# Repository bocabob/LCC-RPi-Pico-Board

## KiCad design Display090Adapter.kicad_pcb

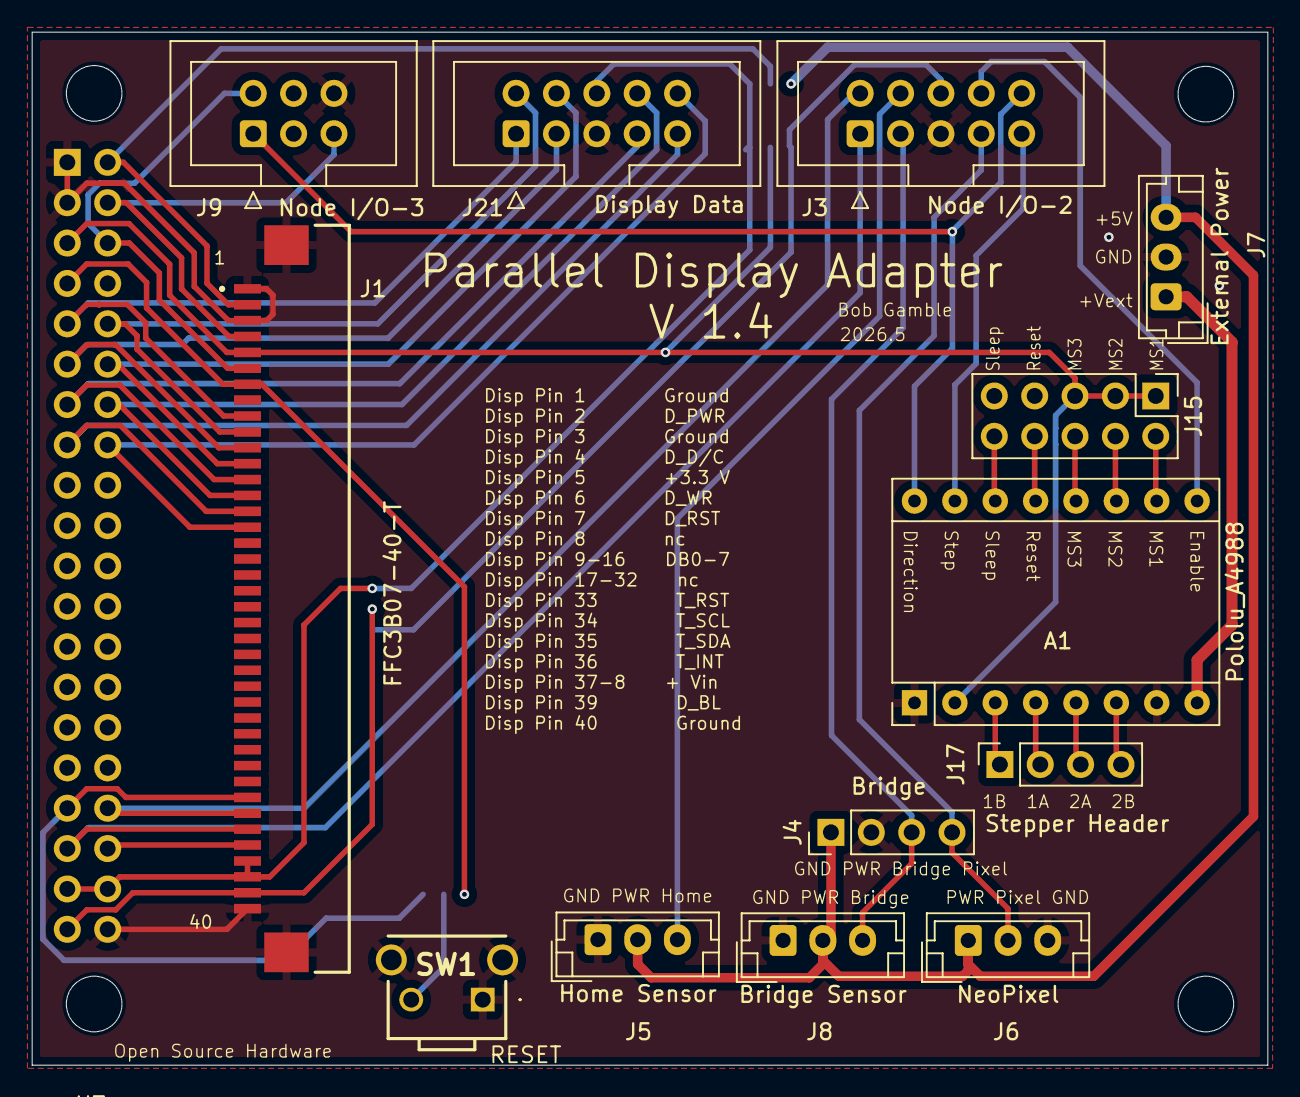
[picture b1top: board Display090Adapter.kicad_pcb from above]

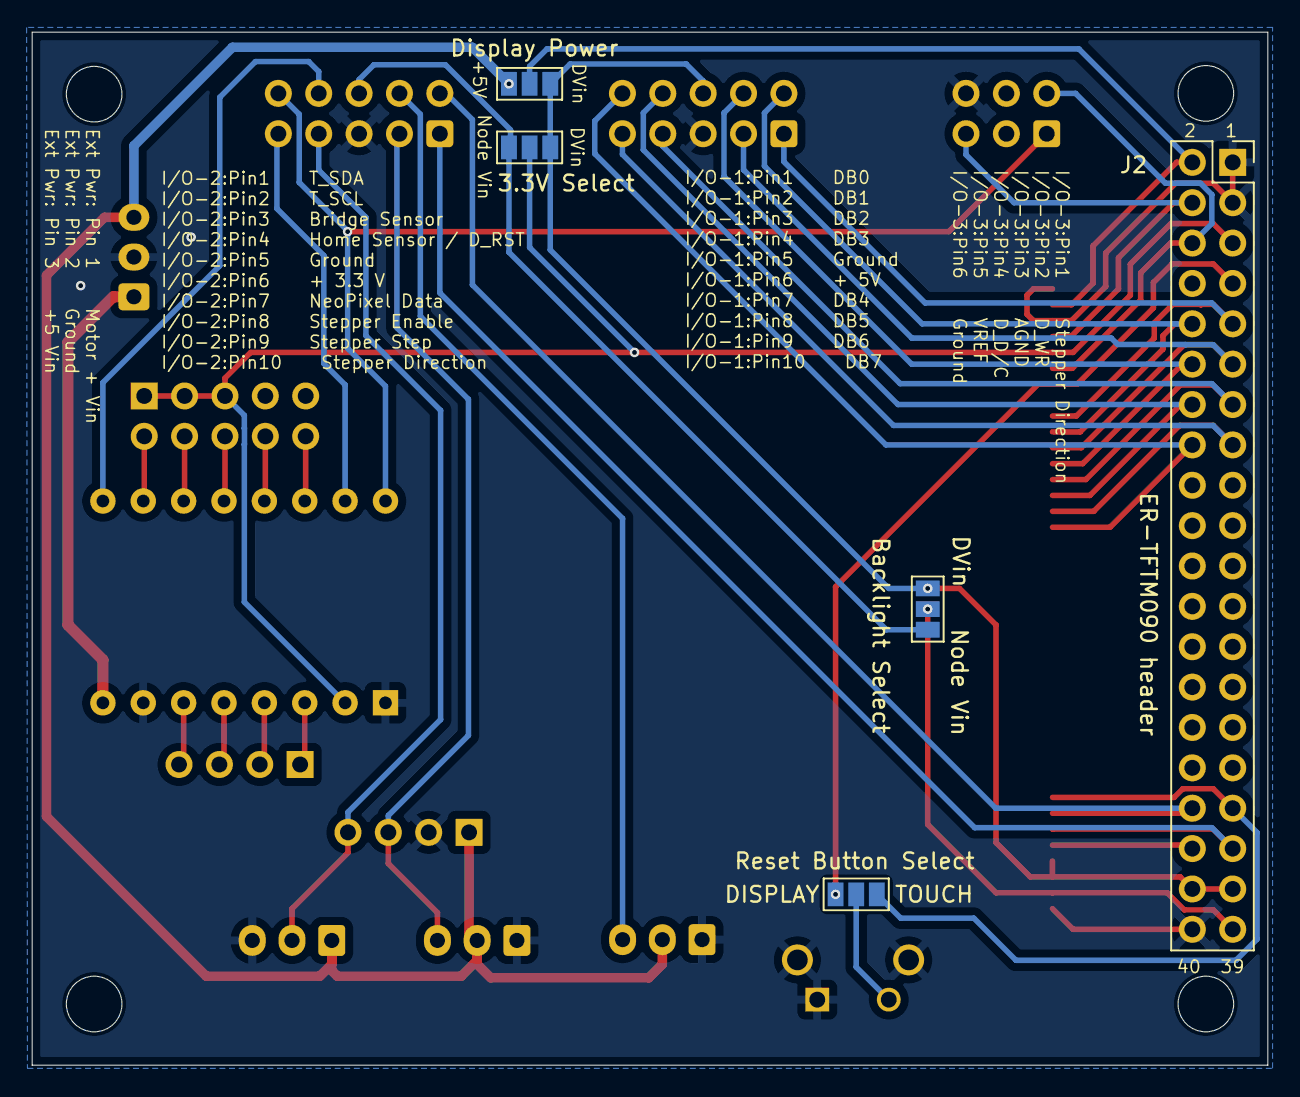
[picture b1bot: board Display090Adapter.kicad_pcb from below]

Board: 2 copper layers, 77.8 x 65.0 mm, 22 parts (5 on the bottom side), 39 nets.

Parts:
A1: Pololu_A4988; Pololu_Breakout-16_15.2x20.3mm
H1, H2, H3, H4: MountingHole; MountingHole_3.5mm
J1: FFC3B07-40-T; GCT_FFC3B07-40-T
J2: ER-TFTM090 header; PinSocket_2x20_P2.54mm_Vertical
J3: Node I/O-2; IDC-Header_2x05_P2.54mm_Vertical
J4: Bridge; PinHeader_1x04_P2.54mm_Vertical
J5: Home Sensor; JST_EH_B3B-EH-A_1x03_P2.50mm_Vertical
J6: NeoPixel; JST_EH_B3B-EH-A_1x03_P2.50mm_Vertical
J7: External Power; JST_EH_B3B-EH-A_1x03_P2.50mm_Vertical
J8: Bridge Sensor; JST_EH_B3B-EH-A_1x03_P2.50mm_Vertical
J9: Node I/O-3; IDC-Header_2x03_P2.54mm_Vertical
J15: Conn_02x05_Odd_Even; PinHeader_2x05_P2.54mm_Vertical
J17: Stepper Header; PinSocket_1x04_P2.54mm_Vertical
J21: Display Data; IDC-Header_2x05_P2.54mm_Vertical
JP1: Backlight Select; SolderJumper-3_P1.3mm_Open_Pad1.0x1.5mm_NumberLabels
JP2: Display Power; SolderJumper-3_P1.3mm_Open_Pad1.0x1.5mm_NumberLabels
JP3: Reset Button Select; SolderJumper-3_P1.3mm_Open_Pad1.0x1.5mm_NumberLabels
JP4: 3.3V Select; SolderJumper-3_P1.3mm_Open_Pad1.0x1.5mm_NumberLabels
SW1: Display Reset; TS1167443BK160RAD

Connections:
+3V3: A1.2 (VDD), J1.5, J2.5, J15.1, J15.3, J15.5, JP4.2 (C)
+5V: J4.1, J5.2, J6.1, J7.3, J8.2, JP2.3 (B)
+VIN: J1.37, J1.38, J2.37, J2.38, J21.6, JP1.1 (A), JP2.1 (A), JP4.1 (A)
BRIDGE: J3.3, J4.3, J8.3
DB0: J1.9, J2.9, J21.1
DB1: J1.10, J2.10, J21.2
DB2: J1.11, J2.11, J21.3
DB3: J1.12, J2.12, J21.4
DB4: J1.13, J2.13, J21.7
DB5: J1.14, J2.14, J21.8
DB6: J1.15, J2.15, J21.9
DB7: J1.16, J2.16, J21.10
DIRECTION: A1.16 (DIR), J3.10, J9.1
D_BL: J1.39, J2.39, JP1.2 (C)
D_D/C: J1.4, J2.4, J9.5
D_PWR: J1.2, J2.2, JP2.2 (C)
D_RST: J1.7, J2.7, JP3.3 (B)
D_WR: J1.6, J2.6, J9.2
ENABLE: A1.9 (~ENABLE), J3.8
GND: A1.1 (GND), A1.7 (GND), J1.1, J1.3, J1.40, J1.S1 (SHIELD), J1.S2 (SHIELD), J2.1, J2.3, J2.40, J3.5, J4.2, J5.1, J6.3, J7.2, J8.1, J9.6, J21.5, SW1.1 (COM), SW1.3 (GND_1), SW1.4 (GND_2)
GP19: J3.4, J5.3
GP20: J3.7, J4.4, J6.2
GP22: A1.15 (STEP), J3.9
unnamed: A1.4 (1A), J17.2
unnamed: A1.3 (1B), J17.1
unnamed: A1.5 (2A), J17.3
unnamed: A1.6 (2B), J17.4
unnamed: A1.10 (MS1), J15.2
unnamed: A1.11 (MS2), J15.4
unnamed: A1.12 (MS3), J15.6
unnamed: A1.13 (~RESET), J15.8
unnamed: A1.14 (~SLEEP), J15.10
unnamed: JP3.2 (C), SW1.2 (NO)
SCL0: J1.34, J2.34, J3.2
SDA0: J1.35, J2.35, J3.1
SVin: J3.6, JP1.3 (B), JP4.3 (B)
T_INT: J1.36, J2.36
T_RST: J1.33, J2.33, JP3.1 (A)
VEXT: A1.8 (VMOT), J7.1

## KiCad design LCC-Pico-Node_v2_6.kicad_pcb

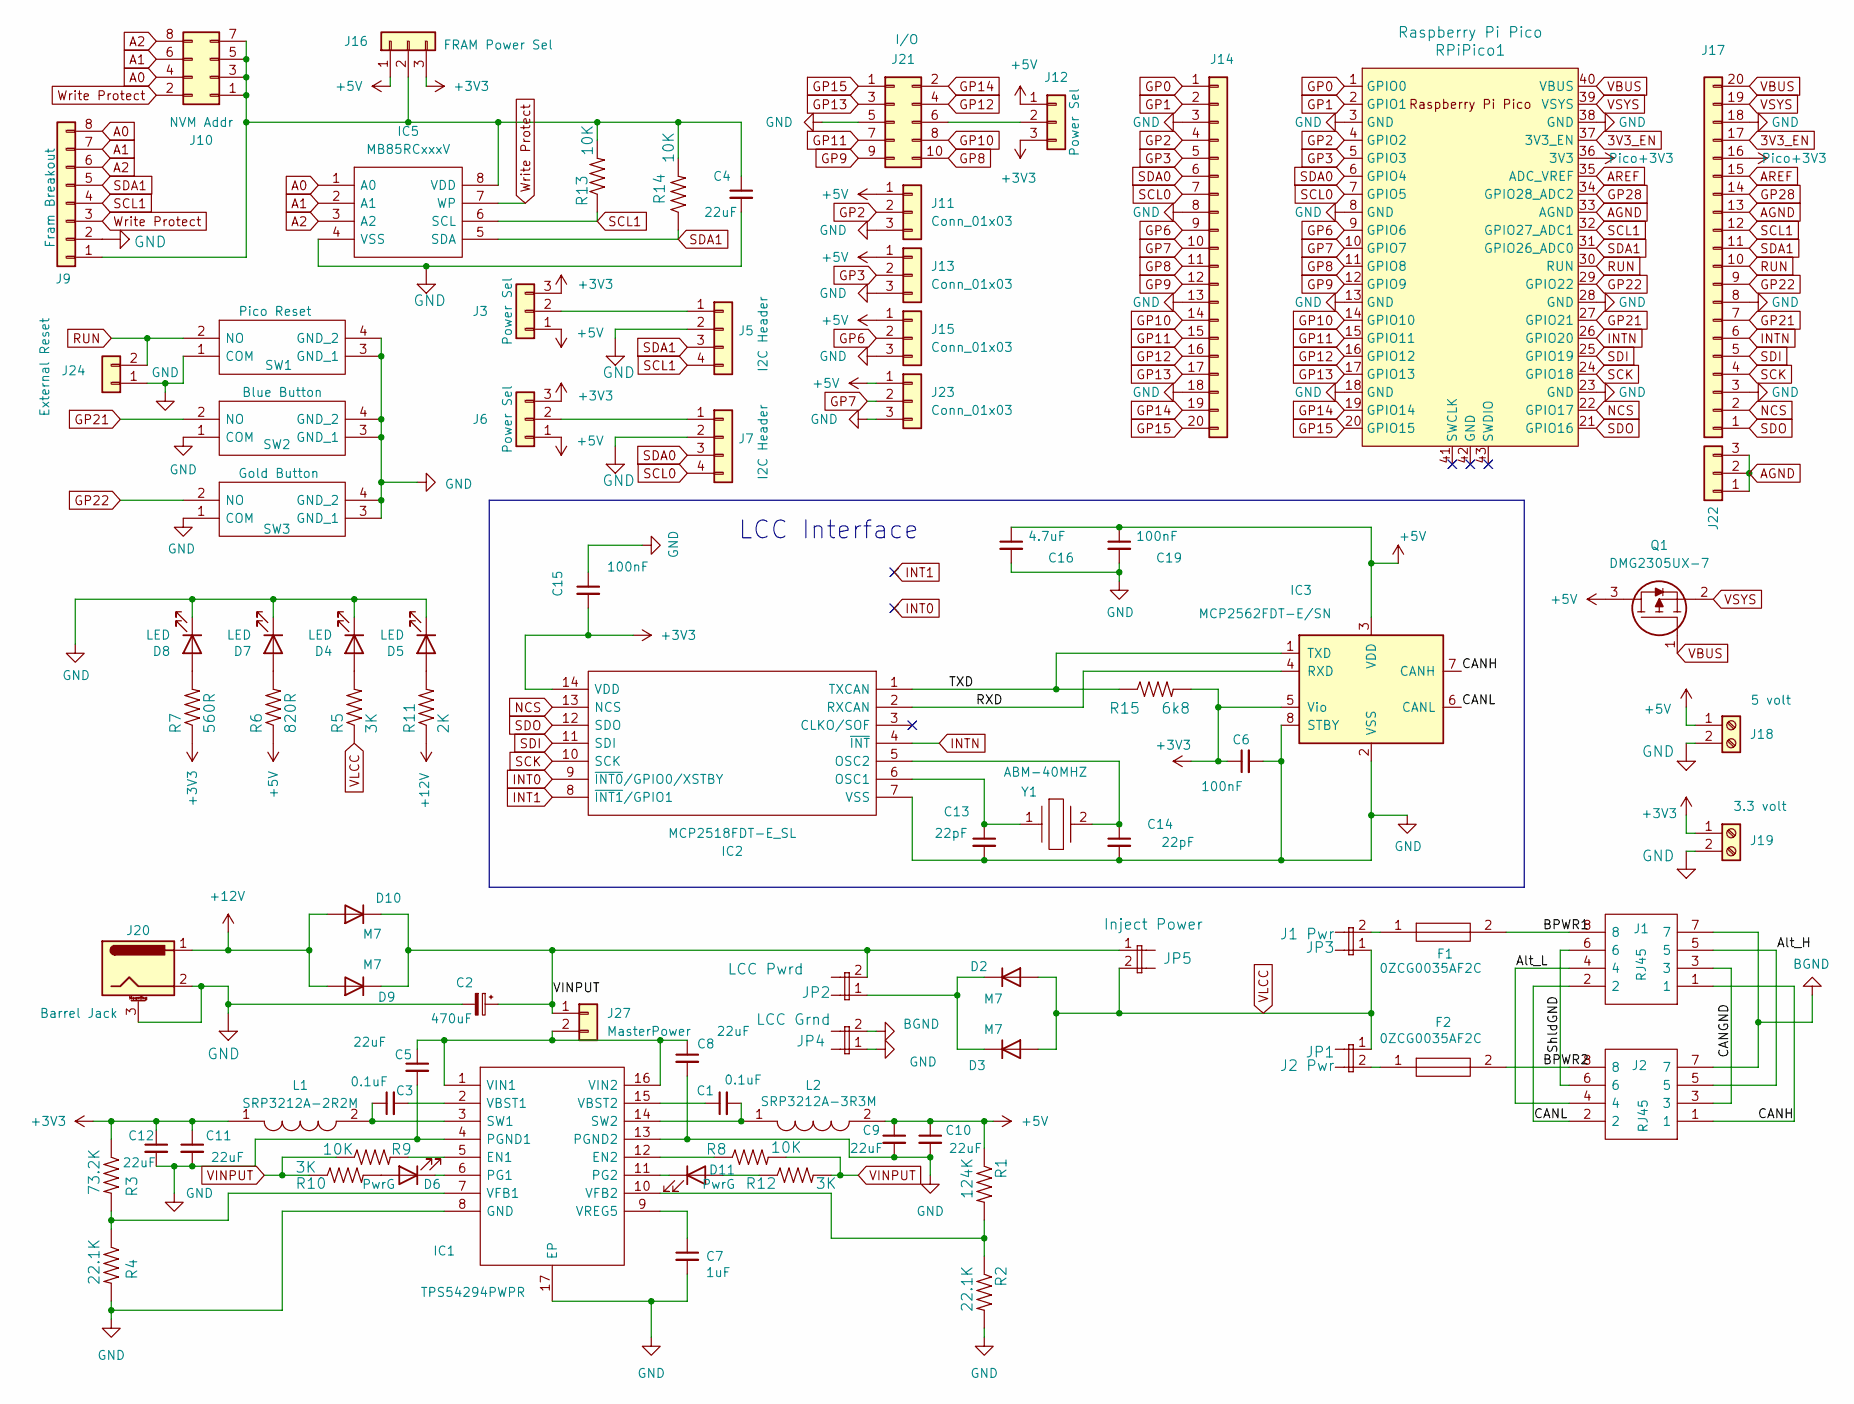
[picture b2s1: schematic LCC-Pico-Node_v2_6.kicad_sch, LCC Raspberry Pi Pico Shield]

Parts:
C1, C3: 0.1uF; C_1206_3216Metric_Pad1.33x1.80mm_HandSolder
C2: 470uF; CP_Radial_D8.0mm_P3.50mm
C4, C5, C8, C9, C10, C11, C12: 22uF; C_1206_3216Metric_Pad1.33x1.80mm_HandSolder
C6, C15, C19: 100nF; C_1206_3216Metric_Pad1.33x1.80mm_HandSolder
C7: 1uF; C_1206_3216Metric_Pad1.33x1.80mm_HandSolder
C13, C14: 22pF; C_1206_3216Metric_Pad1.33x1.80mm_HandSolder
C16: 4.7uF; C_1206_3216Metric_Pad1.33x1.80mm_HandSolder
D2, D3, D9, D10: M7; DIOM5327X240N
D4, D5, D7, D8: LED; LED_1206_3216Metric_Pad1.42x1.75mm_HandSolder
D6, D11: PwrG; LED_1206_3216Metric_Pad1.42x1.75mm_HandSolder
F1, F2: 0ZCG0035AF2C; FUSC4632X70N; Mouser Part Number 530-0ZCG0035AF2C
IC1: TPS54294PWPR; SOP65P640X120-17N; Mouser Part Number 595-TPS54294PWPR
IC2: MCP2518FDT-E_SL; SOIC-14_3.9x8.7mm_P1.27mm; Mouser Part Number 579-MCP2518FDT-E/SL
IC3: MCP2562FDT-E/SN; SOIC-8_3.9x4.9mm_P1.27mm; Mouser Part Number 771-TJA1042T/3/1J
IC5: MB85RCxxxV; SOIC127P600X175-8N; Mouser Part Number 249-MB85RC256VPNJNE1
J1, J2: RJ45; MTJ880X1; Mouser Part Number 737-MTJ-880X1
J3, J6, J12: Power Sel; PinHeader_1x03_P2.54mm_Vertical
J5, J7: I2C Header; PinSocket_1x04_P2.54mm_Vertical
J9: Fram Breakout; PinHeader_1x08_P2.54mm_Vertical
J10: NVM Addr; PinHeader_2x04_P2.54mm_Vertical
J11, J13, J15, J23: Conn_01x03; JST_XH_B3B-XH-A_1x03_P2.50mm_Vertical
J14, J17: Conn_01x20; PinHeader_1x20_P2.54mm_Vertical
J16: FRAM Power Sel; SolderJumper-3_P1.3mm_Open_RoundedPad1.0x1.5mm
J18: 5 volt; TerminalBlock_TE_282834-2_1x02_P2.54mm_Horizontal
J19: 3.3 volt; TerminalBlock_TE_282834-2_1x02_P2.54mm_Horizontal
J20: Barrel Jack; BarrelJack_Horizontal
J21: I/O; IDC-Header_2x05_P2.54mm_Vertical
J22: AGND; PinHeader_1x03_P2.54mm_Vertical
J24: External Reset; PinHeader_1x02_P2.54mm_Vertical
J27: MasterPower; PinHeader_1x02_P2.54mm_Vertical
JP1: J2 Pwr; PinHeader_1x02_P2.54mm_Vertical
JP2: LCC Pwrd; PinHeader_1x02_P2.54mm_Vertical
JP3: J1 Pwr; PinHeader_1x02_P2.54mm_Vertical
JP4: LCC Grnd; PinHeader_1x02_P2.54mm_Vertical
JP5: Inject Power; PinHeader_1x02_P2.54mm_Vertical
L1: SRP3212A-2R2M; INDC3225X120N; Mouser Part Number 652-SRP3212A-3R3M
L2: SRP3212A-3R3M; INDC3225X120N; Mouser Part Number 652-SRP3212A-3R3M
Q1: DMG2305UX-7; SOT96P240X115-3N; Mouser Part Number 621-DMG2305UX-7
R1: 124K; R_1206_3216Metric_Pad1.30x1.75mm_HandSolder
R2, R4: 22.1K; R_1206_3216Metric_Pad1.30x1.75mm_HandSolder
R3: 73.2K; R_1206_3216Metric_Pad1.30x1.75mm_HandSolder
R5, R10, R12: 3K; R_1206_3216Metric_Pad1.30x1.75mm_HandSolder
R6: 820R; R_1206_3216Metric_Pad1.30x1.75mm_HandSolder
R7: 560R; R_1206_3216Metric_Pad1.30x1.75mm_HandSolder
R8, R9, R13, R14: 10K; R_1206_3216Metric_Pad1.30x1.75mm_HandSolder
R11: 2K; R_1206_3216Metric_Pad1.30x1.75mm_HandSolder
R15: 6k8; R_1206_3216Metric_Pad1.30x1.75mm_HandSolder
RPiPico1: Raspberry Pi Pico; RPi_Pico_SMD_TH; PARTREV 12/May/2017
SW1: Pico Reset; TS1167443BK160RAD; Mouser Part Number 179-TS1167443160RAD
SW2: Blue Button; TS1167443BK160RAD; Mouser Part Number 179-TS1167443160RAD
SW3: Gold Button; TS1167443BK160RAD; Mouser Part Number 179-TS1167443160RAD
Y1: ABM-40MHZ; ABM3; Mouser Part Number 815-ABL-40-B2F

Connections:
3V3_EN: J17.17, RPiPico1.37 (3V3_EN)
+3V3: C6.1, C11.1, C12.1, C15.2, IC2.14 (VDD), IC3.5 (Vio), J3.3, J6.3, J12.3, J16.3, J19.1, L1.1, R3.1, R7.1, R15.2
+5V: C9.1, C10.1, C16.1, C19.1, IC3.3 (VDD), J3.1, J6.1, J11.1, J12.1, J13.1, J15.1, J16.1, J18.1, J23.1, L2.2, Q1.3, R1.1, R6.1
+12V: D9.2 (A), D10.2 (A), J20.1, R11.1
/Alt_H: J1.5, J2.5
/Alt_L: J1.4, J2.4
/BPWR1: F1.2, J1.8
/BPWR2: F2.2, J2.8
/CANGND: J1.3, J2.3
/CANH: IC3.7 (CANH), J1.1, J2.1
/CANL: IC3.6 (CANL), J1.2, J2.2
/RXD: IC2.2 (RXCAN), IC3.4 (RXD)
/ShldGND: J1.6, J2.6
/TXD: IC2.1 (TXCAN), IC3.1 (TXD), R15.1
A0: IC5.1 (A0), J9.8, J10.4
A1: IC5.2 (A1), J9.7, J10.6
A2: IC5.3 (A2), J9.6, J10.8
AGND: J17.13, J22.1, J22.2, J22.3, RPiPico1.33 (AGND)
AREF: J17.15, RPiPico1.35 (ADC_VREF)
BGND: J1.7, J2.7, JP4.2
GND: C2.2, C4.2, C5.2, C6.2, C7.2, C8.2, C9.2, C10.2, C11.2, C12.2, C13.2, C14.2, C15.1, C16.2, C19.2, D4.1 (K), D5.1 (K), D7.1 (K), D8.1 (K), IC1.4 (PGND1), IC1.8 (GND), IC1.13 (PGND2), IC1.17 (EP), IC2.7 (VSS), IC3.2 (VSS), IC3.8 (STBY), IC5.4 (VSS), J5.2, J7.2, J9.2, J11.3, J13.3, J14.3, J14.8, J14.13, J14.18, J15.3, J17.3, J17.8, J17.18, J18.2, J19.2, J20.2, J20.3, J21.5, J23.3, J24.1, JP4.1, R2.2, R4.2, RPiPico1.3 (GND), RPiPico1.8 (GND), RPiPico1.13 (GND), RPiPico1.18 (GND), RPiPico1.23 (GND), RPiPico1.28 (GND), RPiPico1.38 (GND), SW1.1 (COM), SW1.3 (GND_1), SW1.4 (GND_2), SW2.1 (COM), SW2.3 (GND_1), SW2.4 (GND_2), SW3.1 (COM), SW3.3 (GND_1), SW3.4 (GND_2)
GP0: J14.1, RPiPico1.1 (GPIO0)
GP1: J14.2, RPiPico1.2 (GPIO1)
GP2: J11.2, J14.4, RPiPico1.4 (GPIO2)
GP3: J13.2, J14.5, RPiPico1.5 (GPIO3)
GP6: J14.9, J15.2, RPiPico1.9 (GPIO6)
GP7: J14.10, J23.2, RPiPico1.10 (GPIO7)
GP8: J14.11, J21.10, RPiPico1.11 (GPIO8)
GP9: J14.12, J21.9, RPiPico1.12 (GPIO9)
GP10: J14.14, J21.8, RPiPico1.14 (GPIO10)
GP11: J14.15, J21.7, RPiPico1.15 (GPIO11)
GP12: J14.16, J21.4, RPiPico1.16 (GPIO12)
GP13: J14.17, J21.3, RPiPico1.17 (GPIO13)
GP14: J14.19, J21.2, RPiPico1.19 (GPIO14)
GP15: J14.20, J21.1, RPiPico1.20 (GPIO15)
GP21: J17.7, RPiPico1.27 (GPIO21), SW2.2 (NO)
GP22: J17.9, RPiPico1.29 (GPIO22), SW3.2 (NO)
GP28: J17.14, RPiPico1.34 (GPIO28_ADC2)
INT0: IC2.9 (~INT0/GPIO0/XSTBY)
INT1: IC2.8 (~INT1/GPIO1)
INTN: IC2.4 (~INT), J17.6, RPiPico1.26 (GPIO20)
NCS: IC2.13 (NCS), J17.2, RPiPico1.22 (GPIO17)
unnamed: D2.1 (K), D3.1 (K), JP2.1
unnamed: D4.2 (A), R5.2
unnamed: D5.2 (A), R11.2
unnamed: D6.2 (A), R10.2
unnamed: D6.1 (K), IC1.6 (PG1)
unnamed: D7.2 (A), R6.2
unnamed: D8.2 (A), R7.2
unnamed: D11.2 (A), R12.1
unnamed: D11.1 (K), IC1.11 (PG2)
unnamed: F1.1, JP3.2
unnamed: F2.1, JP1.2
unnamed: IC1.5 (EN1), R9.2
unnamed: IC1.12 (EN2), R8.1
unnamed: C3.1, IC1.3 (SW1), L1.2
unnamed: C1.2, IC1.14 (SW2), L2.1
unnamed: C3.2, IC1.2 (VBST1)
unnamed: C1.1, IC1.15 (VBST2)
unnamed: IC1.7 (VFB1), R3.2, R4.1
unnamed: IC1.10 (VFB2), R1.2, R2.1
unnamed: C5.1, C8.1, IC1.1 (VIN1), IC1.16 (VIN2), J27.2
unnamed: C7.1, IC1.9 (VREG5)
unnamed: C13.1, IC2.6 (OSC1), Y1.1
unnamed: C14.1, IC2.5 (OSC2), Y1.2
unnamed: C4.1, IC5.8 (VDD), J9.1, J10.1, J10.3, J10.5, J10.7, J16.2, R13.2, R14.2
unnamed: J3.2, J5.1
unnamed: J6.2, J7.1
unnamed: J12.2, J21.6
Pico+3V3: J17.16, RPiPico1.36 (3V3)
RUN: J17.10, J24.2, RPiPico1.30 (RUN), SW1.2 (NO)
SCK: IC2.10 (SCK), J17.4, RPiPico1.24 (GPIO18)
SCL0: J7.4, J14.7, RPiPico1.7 (GPIO5)
SCL1: IC5.6 (SCL), J5.4, J9.4, J17.12, R13.1, RPiPico1.32 (GPIO27_ADC1)
SDA0: J7.3, J14.6, RPiPico1.6 (GPIO4)
SDA1: IC5.5 (SDA), J5.3, J9.5, J17.11, R14.1, RPiPico1.31 (GPIO26_ADC0)
SDI: IC2.11 (SDI), J17.5, RPiPico1.25 (GPIO19)
SDO: IC2.12 (SDO), J17.1, RPiPico1.21 (GPIO16)
VBUS: J17.20, Q1.1, RPiPico1.40 (VBUS)
VINPUT: C2.1, D9.1 (K), D10.1 (K), J27.1, JP2.2, JP5.1, R8.2, R9.1, R10.1, R12.2
VLCC: D2.2 (A), D3.2 (A), JP1.1, JP3.1, JP5.2, R5.1
VSYS: J17.19, Q1.2, RPiPico1.39 (VSYS)
Write Protect: IC5.7 (WP), J9.3, J10.2

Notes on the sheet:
LCC Interface

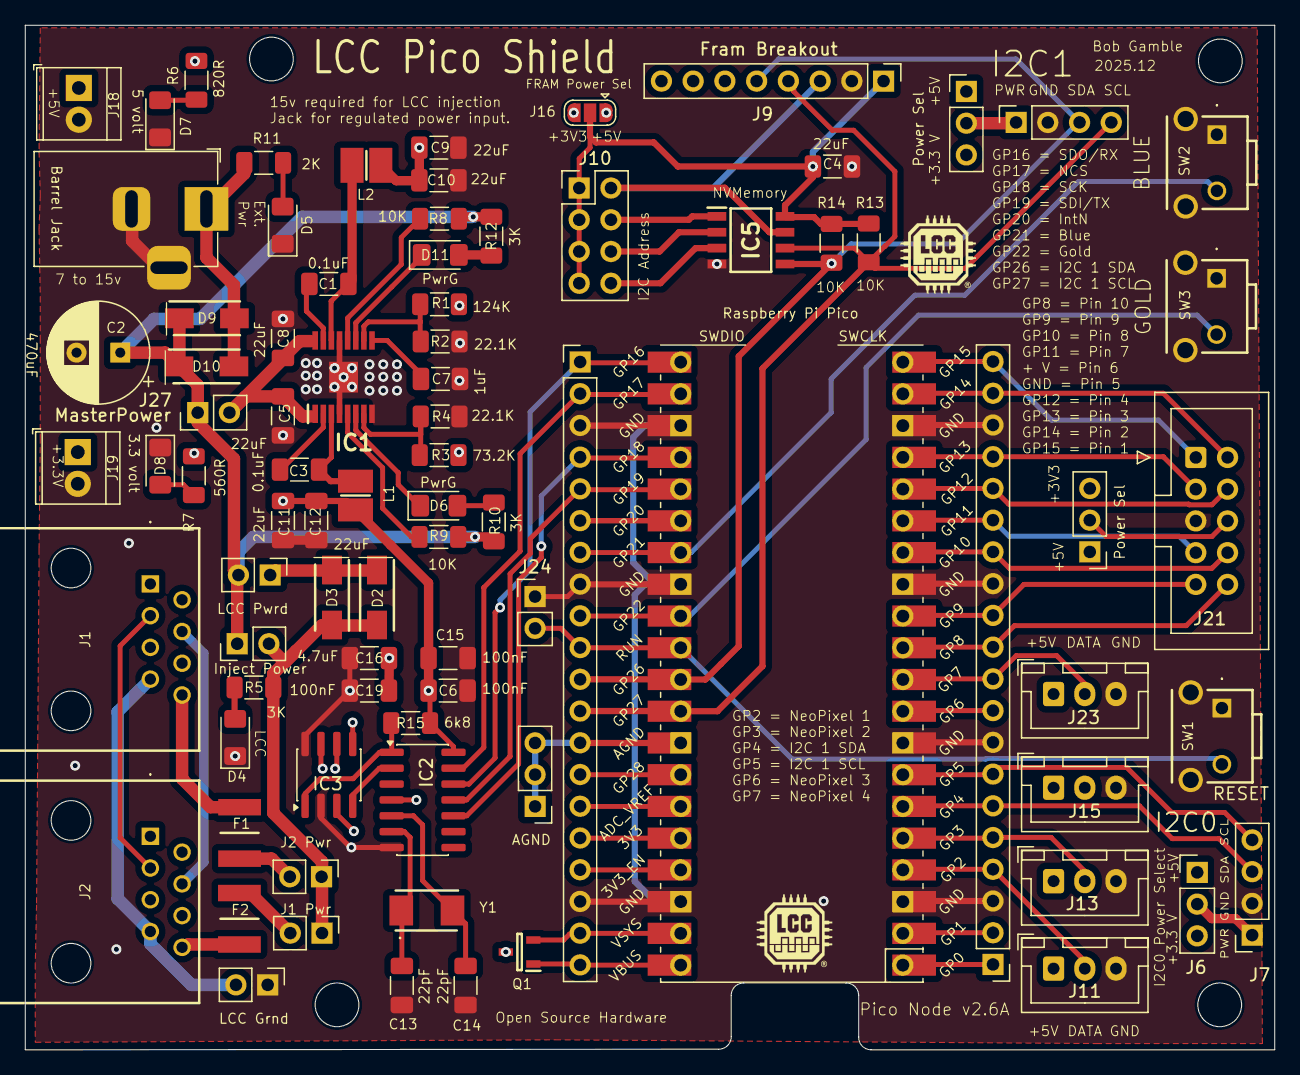
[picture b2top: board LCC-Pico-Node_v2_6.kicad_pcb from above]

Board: 4 copper layers, 100.0 x 82.0 mm, 84 parts (0 on the bottom side), 81 nets.

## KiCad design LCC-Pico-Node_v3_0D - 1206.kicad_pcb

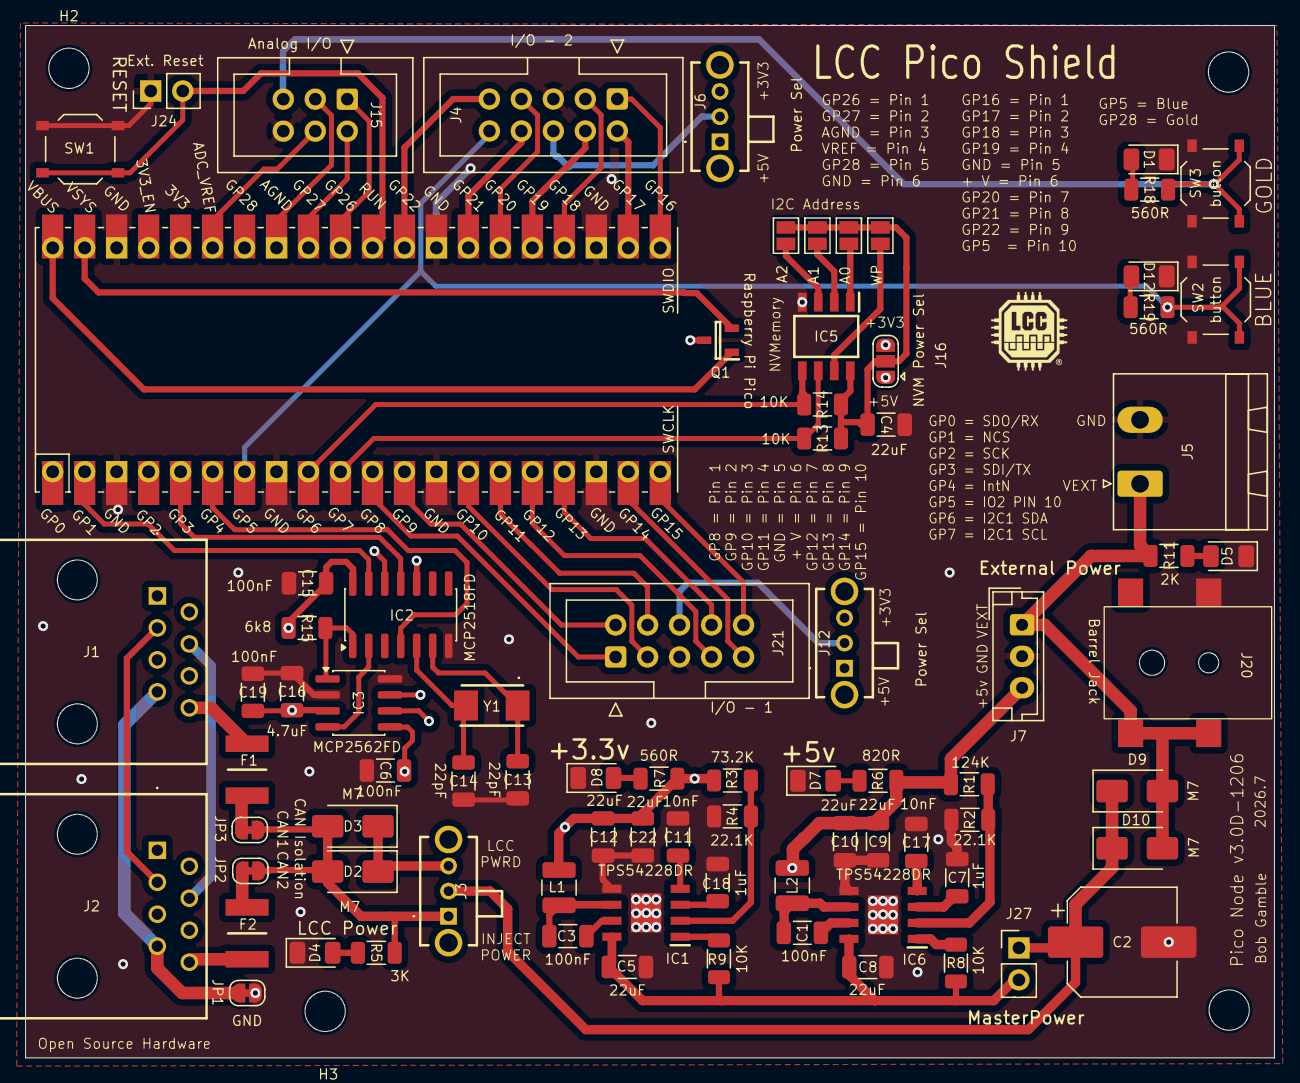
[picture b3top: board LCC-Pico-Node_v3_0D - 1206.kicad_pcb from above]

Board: 4 copper layers, 99.2 x 82.0 mm, 85 parts (0 on the bottom side), 79 nets.

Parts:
C1, C3, C6, C15, C19: 100nF; C_1206_3216Metric
C2: 470uF; CP_Elec_8x10.5
C4, C5, C8, C9, C10, C11, C12: 22uF; C_1206_3216Metric
C7, C18: 1uF; C_1206_3216Metric
C13, C14: 22pF; C_1206_3216Metric
C16: 4.7uF; C_1206_3216Metric
C17, C22: 10nF; C_1206_3216Metric
D1, D4, D5, D7, D8, D12: LED; LED_1206_3216Metric
D2, D3, D9, D10: M7; D_SMA
F1, F2: 0ZCG0035AF2C; FUSC4632X70N
H1, H2, H3, H4: MountingHole; MountingHole_3.2mm_M3
IC1, IC6: TPS54228DR; SOIC127P600X170-9N
IC2: MCP2518FD; SOIC-14_3.9x8.7mm_P1.27mm
IC3: MCP2562FD; SOIC-8_3.9x4.9mm_P1.27mm
IC5: MB85RCxxxV; SOIC127P600X175-8N
J1, J2: RJ45; MTJ880X1
J3: LCC Pwr Sel; SLW8645872ARAND
J4: I/O - 2; IDC-Header_2x05_P2.54mm_Vertical
J5: External Power; PhoenixContact_MSTBA_2,5_2-G-5,08_1x02_P5.08mm_Horizontal
J6, J12: Power Sel; SLW8645872ARAND
J7: External Power; JST_EH_B3B-EH-A_1x03_P2.50mm_Vertical
J15: Analog I/O; IDC-Header_2x03_P2.54mm_Vertical
J16: NVM Power Sel; SolderJumper-3_P1.3mm_Open_RoundedPad1.0x1.5mm
J20: Barrel Jack; DC-050_SMD
J21: I/O - 1; IDC-Header_2x05_P2.54mm_Vertical
J24: Ext. Reset; PinHeader_1x02_P2.54mm_Vertical
J27: MasterPower; PinHeader_1x02_P2.54mm_Vertical
JP1: GND; SolderJumper-2_P1.3mm_Bridged_RoundedPad1.0x1.5mm
JP2: CAN2; SolderJumper-2_P1.3mm_Bridged_RoundedPad1.0x1.5mm
JP3: CAN1; SolderJumper-2_P1.3mm_Bridged_RoundedPad1.0x1.5mm
JP6: A2; SolderJumper-2_P1.3mm_Open_Pad1.0x1.5mm
JP7: A1; SolderJumper-2_P1.3mm_Open_Pad1.0x1.5mm
JP8: A0; SolderJumper-2_P1.3mm_Open_Pad1.0x1.5mm
JP9: WP; SolderJumper-2_P1.3mm_Open_Pad1.0x1.5mm
L1: 3.3uH; L_1210_3225Metric
L2: 4.7uH; L_1210_3225Metric
Q1: DMG2305UX-7; SOT96P240X115-3N
R1: 124K; R_1206_3216Metric
R2, R4: 22.1K; R_1206_3216Metric
R3: 73.2K; R_1206_3216Metric
R5: 3K; R_1206_3216Metric
R6: 820R; R_1206_3216Metric
R7, R18, R19: 560R; R_1206_3216Metric
R8, R9, R13, R14: 10K; R_1206_3216Metric
R11: 2K; R_1206_3216Metric
R15: 6k8; R_1206_3216Metric
RPiPico1: Raspberry Pi Pico; RPi_Pico_SMD_TH
SW1, SW2, SW3: button; SW_Push_1P1T_XKB_TS-1187A
Y1: ABM-40MHZ; ABM3

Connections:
+3V3: C6.1, C11.1, C12.1, C15.2, IC2.14 (VDD), IC3.5 (Vio), J6.3 (C), J12.3 (C), J16.3 (B), L1.2, R3.1, R7.1, R15.2
+5V: C9.1, C10.1, C16.1, C19.1, IC3.3 (VDD), J6.1 (A), J7.3, J12.1 (A), J16.1 (A), L2.2, Q1.3, R1.2, R6.1
/Alt_H: J1.5, J2.5
/Alt_L: J1.4, J2.4
/BPWR1: F1.2, J1.8
/BPWR2: F2.2, J2.8
/CANGND: J1.3, J2.3
/CANH: IC3.7 (CANH), J1.1, J2.1
/CANL: IC3.6 (CANL), J1.2, J2.2
/RXD: IC2.2 (RXCAN), IC3.4 (RXD)
/ShldGND: J1.6, J2.6
/TXD: IC2.1 (TXCAN), IC3.1 (TXD), R15.1
A0: IC5.1 (A0), JP8.1 (A)
A1: IC5.2 (A1), JP7.1 (A)
A2: IC5.3 (A2), JP6.1 (A)
AGND: J15.3, RPiPico1.33 (AGND)
AREF: J15.4, RPiPico1.35 (ADC_VREF)
BGND: J1.7, J2.7, JP1.2 (B)
GND: C2.2, C4.2, C5.2, C6.2, C7.2, C8.1, C9.2, C10.2, C11.2, C12.2, C13.2, C14.2, C15.1, C16.2, C17.2, C18.2, C19.2, C22.2, D1.1 (K), D4.1 (K), D5.1 (K), D7.1 (K), D8.1 (K), D12.1 (K), IC1.5 (GND), IC1.9 (EP), IC2.7 (VSS), IC3.2 (VSS), IC3.8 (STBY), IC5.4 (VSS), IC6.5 (GND), IC6.9 (EP), J4.5, J5.2, J7.2, J15.6, J20.2, J21.5, J24.1, JP1.1 (A), R2.2, R4.2, RPiPico1.3 (GND), RPiPico1.8 (GND), RPiPico1.13 (GND), RPiPico1.18 (GND), RPiPico1.23 (GND), RPiPico1.28 (GND), RPiPico1.38 (GND), SW1.1 (COM), SW2.1 (COM), SW3.1 (COM)
GP5: J4.10, R19.1, RPiPico1.7 (GPIO5), SW2.2 (NO)
GP8: J21.1, RPiPico1.11 (GPIO8)
GP9: J21.2, RPiPico1.12 (GPIO9)
GP10: J21.3, RPiPico1.14 (GPIO10)
GP11: J21.4, RPiPico1.15 (GPIO11)
GP12: J21.7, RPiPico1.16 (GPIO12)
GP13: J21.8, RPiPico1.17 (GPIO13)
GP14: J21.9, RPiPico1.19 (GPIO14)
GP15: J21.10, RPiPico1.20 (GPIO15)
GP18: J4.3, RPiPico1.24 (GPIO18)
GP19: J4.4, RPiPico1.25 (GPIO19)
GP20: J4.7, RPiPico1.26 (GPIO20)
GP21: J4.8, RPiPico1.27 (GPIO21)
GP22: J4.9, RPiPico1.29 (GPIO22)
GP26: J15.1, RPiPico1.31 (GPIO26_ADC0)
GP27: J15.2, RPiPico1.32 (GPIO27_ADC1)
GP28: J15.5, R18.1, RPiPico1.34 (GPIO28_ADC2), SW3.2 (NO)
INTN: IC2.4 (~INT), RPiPico1.6 (GPIO4)
NCS: IC2.13 (NCS), RPiPico1.2 (GPIO1)
unnamed: D1.2 (A), R18.2
unnamed: D2.1 (K), D3.1 (K), J3.3 (C)
unnamed: D4.2 (A), R5.2
unnamed: D5.2 (A), R11.2
unnamed: D7.2 (A), R6.2
unnamed: D8.2 (A), R7.2
unnamed: C2.1, D9.1 (K), D10.1 (K), J3.2 (B), J27.1
unnamed: D12.2 (A), R19.2
unnamed: IC1.1 (EN), R9.2
unnamed: C22.1, IC1.4 (SS)
unnamed: C3.1, IC1.6 (SW), L1.1
unnamed: C3.2, IC1.7 (VBST)
unnamed: IC1.2 (VFB), R3.2, R4.1
unnamed: C18.1, IC1.3 (VREG5)
unnamed: C13.1, IC2.6 (OSC1), Y1.1
unnamed: C14.1, IC2.5 (OSC2), Y1.2
unnamed: C4.1, IC5.8 (VDD), J16.2 (C), JP6.2 (B), JP7.2 (B), JP8.2 (B), JP9.2 (B), R13.2, R14.2
unnamed: IC6.1 (EN), R8.1
unnamed: C17.1, IC6.4 (SS)
unnamed: C1.2, IC6.6 (SW), L2.1
unnamed: C1.1, IC6.7 (VBST)
unnamed: IC6.2 (VFB), R1.1, R2.1
unnamed: C7.1, IC6.3 (VREG5)
unnamed: J4.6, J6.2 (B)
unnamed: J12.2 (B), J21.6
unnamed: F2.1, JP2.2 (B)
unnamed: F1.1, JP3.2 (B)
RUN: J24.2, RPiPico1.30 (RUN), SW1.2 (NO)
SCK: IC2.10 (SCK), RPiPico1.4 (GPIO2)
SCL0: J4.2, RPiPico1.22 (GPIO17)
SCL1: IC5.6 (SCL), R13.1, RPiPico1.10 (GPIO7)
SDA0: J4.1, RPiPico1.21 (GPIO16)
SDA1: IC5.5 (SDA), R14.1, RPiPico1.9 (GPIO6)
SDI: IC2.11 (SDI), RPiPico1.5 (GPIO3)
SDO: IC2.12 (SDO), RPiPico1.1 (GPIO0)
VBUS: Q1.1, RPiPico1.40 (VBUS)
VEXT: D9.2 (A), D10.2 (A), J5.1, J7.1, J20.1, R11.1
VINPUT: C5.1, C8.2, IC1.8 (VIN), IC6.8 (VIN), J27.2, R8.2, R9.1
VLCC: D2.2 (A), D3.2 (A), J3.1 (A), JP2.1 (A), JP3.1 (A), R5.1
VSYS: Q1.2, RPiPico1.39 (VSYS)
Write Protect: IC5.7 (WP), JP9.1 (A)

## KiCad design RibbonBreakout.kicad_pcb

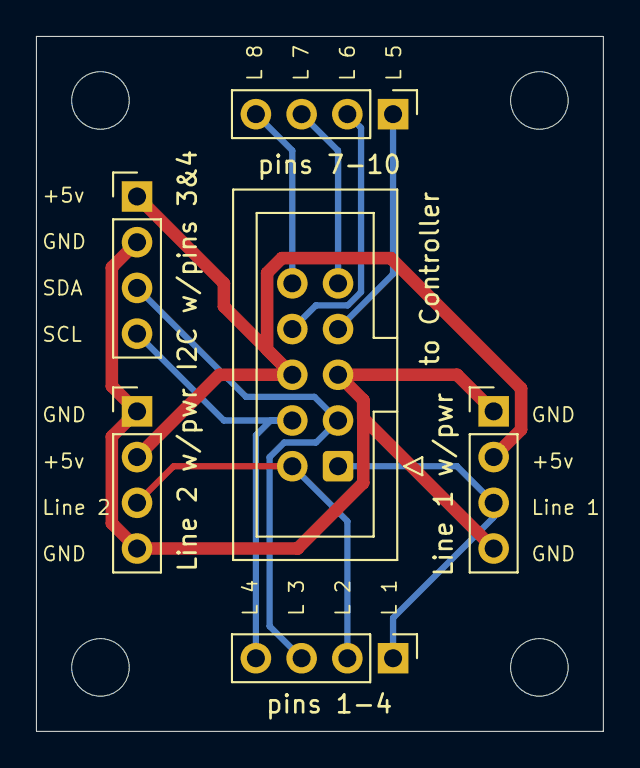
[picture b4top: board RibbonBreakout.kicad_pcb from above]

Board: 2 copper layers, 31.5 x 38.6 mm, 6 parts (0 on the bottom side), 10 nets.

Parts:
J1, J2, J3, J4, J5: PinHeader_1x04_P2.54mm_Vertical
S1: Conn_02x05_Odd_Even; IDC-Header_2x05_P2.54mm_Vertical

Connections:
+5v: J1.2, J2.2, J5.1, S1.6
GND: J1.1, J1.4, J2.1, J2.4, J5.2, S1.5
Line1: J1.3, J3.1, S1.1
Line2: J2.3, J3.2, S1.2
Line3: J3.3, J5.3, S1.3
Line4: J3.4, J5.4, S1.4
Line5: J4.1, S1.7
Line6: J4.2, S1.8
Line7: J4.3, S1.9
Line8: J4.4, S1.10
